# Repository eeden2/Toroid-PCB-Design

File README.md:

# Plasma Toroid Schematic Design

__Currently, this PCB is in the TESTING Stages__

Based off of the Circuit from [Steve Ward](https://docs.google.com/document/d/1AyaO-RaTiaOmyT3-89UxPdrMHEBCCrxb1irZKsVMg_8/edit) and [BackMacSci's Video](https://www.youtube.com/watch?v=GbMAvn7nRWo), I decided to make my own PCB Design for the Circuit.

__All Ideas to the Papers Are Linked Below__

# 3-D View:

# The Parts are as Follows:

- __Variable power supply / 50 - 100 W laptop power supply__

- __16 AWG copper wire or ¼” copper tubing (1 uH inductor)__

- __20-26 AWG copper wire (10 uH inductor) OR__

        (Mouser #:  81-LQH32NH100J23L; Mfr. #: LQH32NH100J23L )

- __2, 0.5W 1k resistors__

        (Mouser #: 652-CHP0805AFX1001EL; Mfr. #: CHP0805AFX-1001ELF )

- __10k potentiometer__

        (Mouser #:  581-601030; Mfr. #: 601030 )

- __100V, 1uF capacitor__

        (Mouser #: 80-C1210C105K1RACTM; Mfr. #: C1210C105K1RACTM ) 

- __4, 6kV, 33 pF ceramic dipped capacitors__

        (Mouser #: 810-CC45SL3JD330JYGN; Mfr. #: CC45SL3JD330JYGNA )  

- __2, 450V, 4.7 nF C0G 0805 SMD capacitors__

        (Mouser #: 810-C2012C0G2W472JAA; Mfr. #: C2012C0G2W472J125AA )

- __FDA18N50 or FDH44N50 Mosfet__

        (Mouser #: 512-FDA18N50; Mfr. #: FDA18N50 )

- __Mosfet hardware (for securing mosfet to the heatsink)__

- __Large heatsink__

- __12V fan__

- __Borosilicate glass globe filled with 15 torr xenon gas__

- __Oscilloscope, multimeter, soldering iron__

# PCB:

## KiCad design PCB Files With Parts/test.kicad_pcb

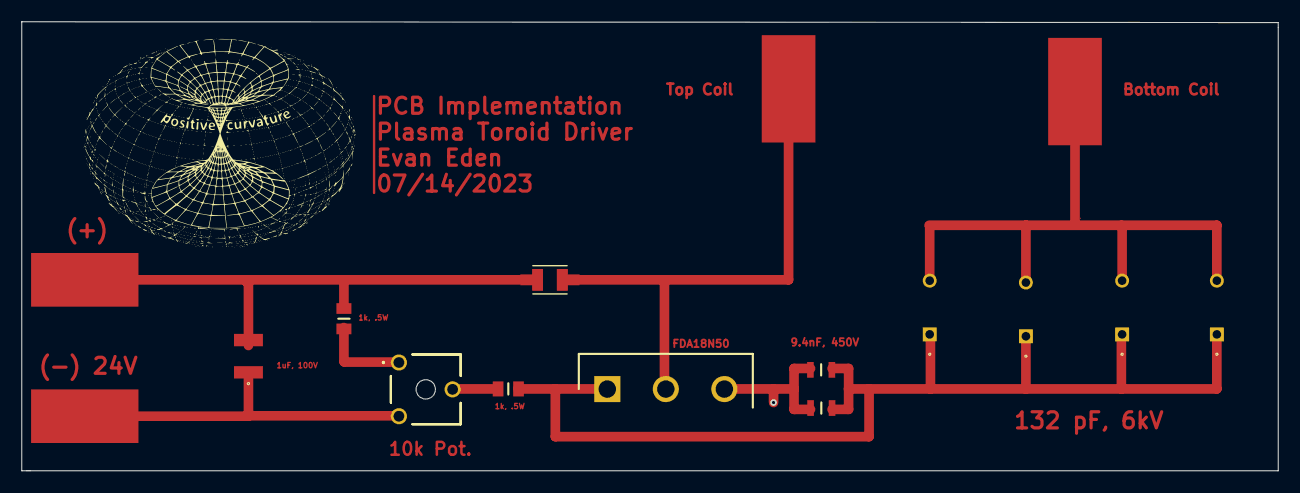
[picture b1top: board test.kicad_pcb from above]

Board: 2 copper layers, 117.0 x 41.8 mm, 12 parts (0 on the bottom side), 8 nets.

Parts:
C1: 100V 1uF; C1210
C3, C4, C5, C6: 33 pF; CC45SL3JD330JYGNA
C8, C9: 4700 pF; CAPC2012X145N
L2: LQH32NH100J23L; IND_LQH32NH100J23L
Q1: FDA18N50; TO545P500X1580X2420-3P
R1, R2: CHP0805AFX-1001ELF; RESC2012X60N
VR1: 601030

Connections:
+VDC: C1.2, L2.1, R2.2
-VDC: C1.1, VR1.3 (CW)
GND: C8.1, C9.1, Q1.3 (S)
unnamed: C3.2, C4.2, C5.2, C6.2
unnamed: L2.2, Q1.2 (D)
unnamed: R2.1, VR1.1 (CCW)
unnamed: R1.1, VR1.2 (WIPER)
Test: C3.1, C4.1, C5.1, C6.1, C8.2, C9.2, Q1.1 (G), R1.2

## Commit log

2023-08-02 V2 is now Printed and currently in testing.
